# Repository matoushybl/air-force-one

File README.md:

# Air Force One - a simple air quality measurement system
Air Force One is a simple air quality measurement systems primarily designed to measure CO2 concentration in multiple rooms of a small apartment. 
It consists of nodes responsible for measuring the data and broadcasting them using BLE advertisements and a bridge which periodically receives the data and publishes them over MQTT for further processing - in this case displaying them in dashboards of Home Assistant.
There are two types of nodes which differ in used hardware and therefore communication protocol. The project was originally developed with the Bluetooth ones in mind, while the ESP32/WiFi one was added only as an experiment.

An overview of the system can be seen in the following image.

## Project structure
* `node-fw` - firmware for the Bluetooth node
* `node-c3` - firmware for the ESP32/WiFi node
* `bridge-fw` - firmware for the Bluetooth bridge
* `shared` - shared library for node and bridge firmware
* `pcb` - design files for the electronics
* `case` - design files for the case

## Hardware
The hardware for this project is based on Nordic's nRF52840 bluetooth enabled MCU. CO2 concentration, temperature and humidity are measured by a Sensirion SCD41 sensor.
The hardware was developed to allow for more features in the future so apart from the SCD41, there are more on-board parts:
* QSPI flash for measurements logging
* 4 buttons
* a connector and a hardware switch for connecting external battery (the circuitry however was not optimized for low-power even though it is well supported with embassy on nRF52)
* SHT4x sensor for more precise temperature and humidity measurements (the sensors were either badly wired or damaged on prototype boards, so no support for them was added)
* broken out pins allowing for some extensibility

The nodes and the bridge do not differ hardware wise, but the prototype bridge didn't have assembled anything other than the nRF52 module, LDO and USB circuitry to save parts, so no measurement support is available in the bridge firmware. The difference between them can be seen in the following image.

For firmware flashing a SWD probe is required. The programming connector on-board is the 10-pin Cortex-M debug connector with 1.27 mm pitch. An example of a usable probe with the same connector is the [hs-probe](https://github.com/probe-rs/hs-probe). 

There is also a case available fitting the PCB shape.

## Firmware
The firmware for both the node and the bridge is written in Rust and utilizes [embassy](https://embassy.dev) async framework as well as [nrf-softdevice](https://github.com/embassy-rs/nrf-softdevice) for bluetooth support.
As such it is assumed that you have standard embedded Rust development tools installed - such as [probe-rs](https://probe.rs/).

To use the firmware, Nordic's softdevice must first be flashed to the MCU.

1. First download the Softdevice from [here](https://www.nordicsemi.com/Software-and-tools/Software/S140/Download)
2. Mass erase the MCU `probe-rs erase --chip nrf52840_xxAA`
3. Flash the softdevice `probe-rs download --verify --format hex --chip nRF52840_xxAA s140_nrf52_7.X.X_softdevice.hex`

> Mass erasing the MCU has an unfortunate side effect of disabling reset pin. The firmwares in this repository reenable this functionality on startup.

Both of the firmware have their panic behavior configured to automatic reset, for development purposes however, it is better to switch to `panic-probe` panic handler using the 'dev' feature that can be passed to cargo.

### Node Firmware
Firmware for the node periodically reads data from the SCD41 sensor and updates Manufacturer Specific Data that are part of BLE advertisement.
For accessing the SCD41 sensor, the firmware uses the [sensirion-async](https://github.com/matoushybl/sensirion-async) library.

Flashing the firmware can be done in the `node-fw` directory by running `cargo run --release`.

### Bridge Firmware
Firmware for the bridge scans for available nodes and reads the Manufacturer Specific data part of the node's advertisement. A CDC-NCM bridge is utilized to establish a connection to a MQTT broker. Data read from the scans are then published via the broker. Static IP addresses are utilized in this configuration.

Flashing the firmware can be done in the `bridge-fw` directory by running `cargo run --release`.

## Experimental ESP32/WiFi node
As an experiment a node based on ESP32-C3 was developed. The firmware for this node is written using a similar technological stack as the nRf52 firmware - Rust and embassy. The firmware is located in the `node-c3` directory. A defining difference is that this node directly accesses the MQTT broker, making it much more simpler and hopefully more reliable.

This node also utilizes off-the-shelf hardware, so no custom PCB is requried. In this case [this ESP32-C3 board](https://www.laskakit.cz/laskkit-esp-12-board/?variantId=10482) [this SCD41 breakout board](https://www.laskakit.cz/laskakit-scd41-senzor-co2--teploty-a-vlhkosti-vzduchu/) were used, but any development kits should work the same (apart from assigning pins for the I2C).

When building the firmware SSID, password and MQTT broker address must be set as environent variables. Refer to the respective `main.rs` for environment variable names.

> As of time of publishing, the firmware uses unreleased esp-rs crates - `esp-backtrace` and `esp-println` alongside with `espflash` tool. These were used to add support for defmt.

## Accessing the measured data

### Configuring the network interface
The network interface can either be configured one-time using the `ip` command or using netplan on Ubuntu using a similar config to the one below. Using netplan has an advantage of the configuration being persistent over reboots and bridge reconnects.

The following config sets a static IP on the USB CDC-NCM interface.

```
network:
  version: 2
  renderer: networkd
  ethernets:
      enx888888888888:
          optional: true
          dhcp4: no
          addresses: [10.42.0.1/24]
```

### MQTT
The bridge firmware expects an MQTT broker running on the computer it is connected to. A simple way to spin up the broker is to use docker.
```
docker run -it -p 1883:1883 -v $(pwd)/mosquitto.conf:/mosquitto/config/mosquitto.conf eclipse-mosquitto
```

The bridge expects the broker to run without authentication, which can be achieved by the following `mosquitto.conf`:
```
listener 1883
allow_anonymous true
```

### Home Assistant
Once the measured data are published to the broker, MQTT integration in Home Assistant can be used to access the measured data. A sample Home Assistant configuration can be found below.

```yaml
mqtt:
  sensor:
    - name: "Bedroom - co2"
      state_topic: "afo-1"
      unit_of_measurement: "PPM"
      value_template: "{{ value_json.co2 }}"
      device_class: "carbon_dioxide"
    - name: "Bedroom - humidity"
      state_topic: "afo-1"
      unit_of_measurement: "%"
      value_template: "{{ value_json.humidity }}"
      device_class: "humidity"
    - name: "Bedroom - temperature"
      state_topic: "afo-1"
      unit_of_measurement: "°C"
      suggested_display_precision: 1
      value_template: "{{ value_json.temperature }}"
      device_class: "temperature"
    - name: "Living room - co2"
      state_topic: "afo-0"
      unit_of_measurement: "PPM"
      value_template: "{{ value_json.co2 }}"
      device_class: "carbon_dioxide"
    - name: "Living room - humidity"
      state_topic: "afo-0"
      unit_of_measurement: "%"
      value_template: "{{ value_json.humidity }}"
      device_class: "humidity"
    - name: "Living room - temperature"
      state_topic: "afo-0"
      unit_of_measurement: "°C"
      suggested_display_precision: 1
      value_template: "{{ value_json.temperature }}"
      device_class: "temperature"
```

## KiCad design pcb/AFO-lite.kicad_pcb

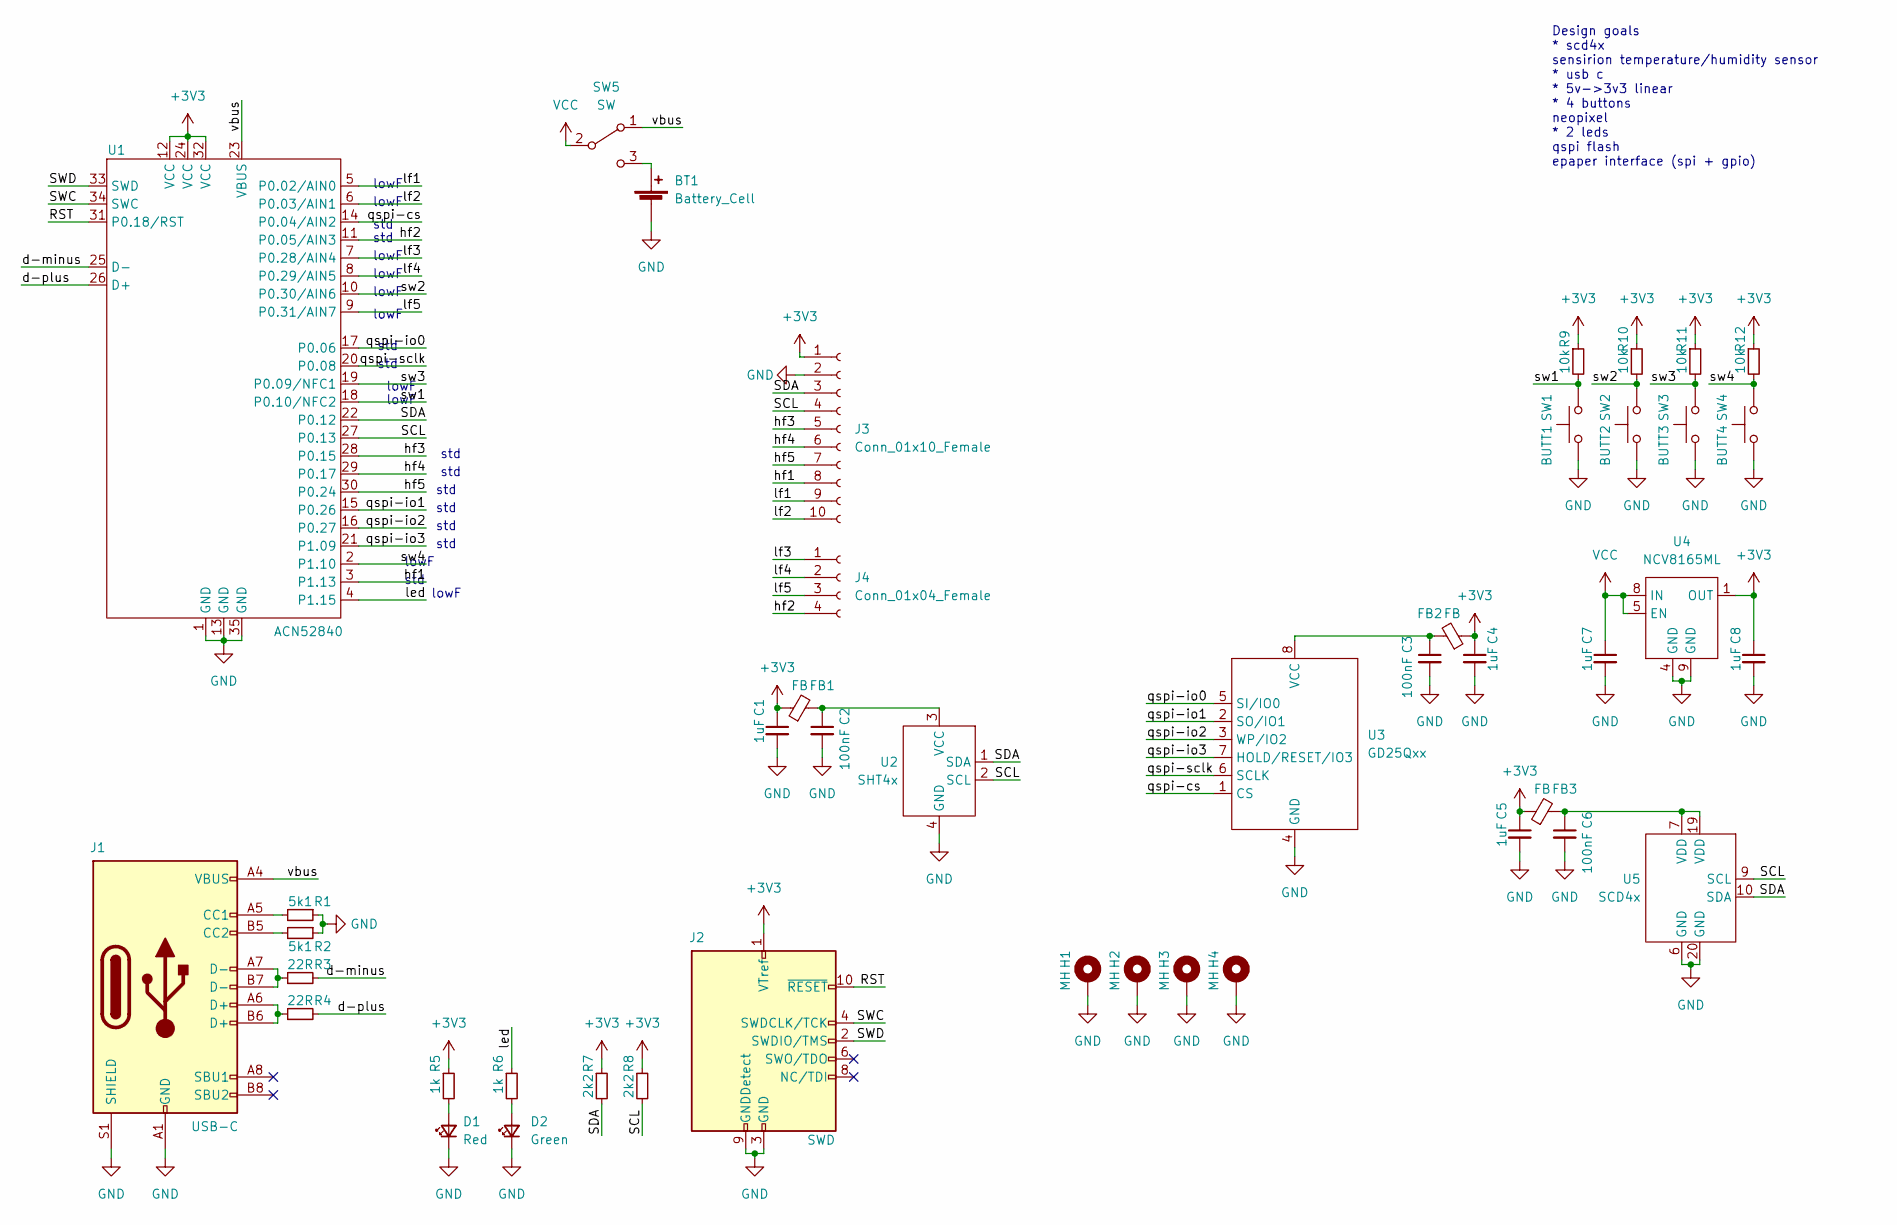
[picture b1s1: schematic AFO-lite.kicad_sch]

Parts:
BT1: Battery_Cell; PinHeader_1x02_P2.54mm_Horizontal
C1, C4, C5, C7, C8: 1uF; C_0805_2012Metric_Pad1.18x1.45mm_HandSolder
C2, C3, C6: 100nF; C_0603_1608Metric_Pad1.08x0.95mm_HandSolder
D1: Red; LED_0805_2012Metric_Pad1.15x1.40mm_HandSolder
D2: Green; LED_0805_2012Metric_Pad1.15x1.40mm_HandSolder
FB1, FB2, FB3: FB; L_0805_2012Metric_Pad1.15x1.40mm_HandSolder
H1, H2, H3, H4: MH; MountingHole_2.5mm_Pad_Via
J1: USB-C; USB_C_Receptacle_XKB_U262-16XN-4BVC11
J2: SWD; PinHeader_2x05_P1.27mm_Vertical_SMD
J3: Conn_01x10_Female; PinHeader_1x10_P2.54mm_Vertical
J4: Conn_01x04_Female; PinHeader_1x04_P2.54mm_Vertical
R1, R2: 5k1; R_0603_1608Metric_Pad0.98x0.95mm_HandSolder
R3, R4: 22R; R_0603_1608Metric_Pad0.98x0.95mm_HandSolder
R5, R6: 1k; R_0603_1608Metric_Pad0.98x0.95mm_HandSolder
R7, R8: 2k2; R_0603_1608Metric_Pad0.98x0.95mm_HandSolder
R9, R10, R11, R12: 10k; R_0603_1608Metric_Pad0.98x0.95mm_HandSolder
SW1: BUTT1; SW_SPST_B3U-3000P
SW2: BUTT2; SW_SPST_B3U-3000P
SW3: BUTT3; SW_SPST_B3U-3000P
SW4: BUTT4; SW_SPST_B3U-3000P
SW5: SW; SW_SPDT_PCM12
U1: ACN52840; ANC52840
U2: SHT4x
U3: GD25Qxx; SOP-8_5.28x5.23mm_P1.27mm
U4: NCV8165ML; DFN-8-1EP_3x3mm_P0.65mm_EP1.55x2.4mm
U5: SCD4x

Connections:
+3V3: C1.1, C4.1, C5.1, C8.1, FB1.1, FB2.1, FB3.1, J2.1 (VTref), J3.1, R5.1, R7.1, R8.1, R9.1, R10.1, R11.1, R12.1, U1.12 (VCC), U1.24 (VCC), U1.32 (VCC), U4.1 (OUT)
/RST: J2.10 (~RESET), U1.31 (P0.18/RST)
/SCL: J3.4, R8.2, U1.27 (P0.13), U2.2 (SCL), U5.9 (SCL)
/SDA: J3.3, R7.2, U1.22 (P0.12), U2.1 (SDA), U5.10 (SDA)
/SWC: J2.4 (SWDCLK/TCK), U1.34 (SWC)
/SWD: J2.2 (SWDIO/TMS), U1.33 (SWD)
/d-minus: R3.2, U1.25 (D-)
/d-plus: R4.2, U1.26 (D+)
/hf1: J3.8, U1.3 (P1.13)
/hf2: J4.4, U1.11 (P0.05/AIN3)
/hf3: J3.5, U1.28 (P0.15)
/hf4: J3.6, U1.29 (P0.17)
/hf5: J3.7, U1.30 (P0.24)
/led: R6.1, U1.4 (P1.15)
/lf1: J3.9, U1.5 (P0.02/AIN0)
/lf2: J3.10, U1.6 (P0.03/AIN1)
/lf3: J4.1, U1.7 (P0.28/AIN4)
/lf4: J4.2, U1.8 (P0.29/AIN5)
/lf5: J4.3, U1.9 (P0.31/AIN7)
/qspi-cs: U1.14 (P0.04/AIN2), U3.1 (CS)
/qspi-io0: U1.17 (P0.06), U3.5 (SI/IO0)
/qspi-io1: U1.15 (P0.26), U3.2 (SO/IO1)
/qspi-io2: U1.16 (P0.27), U3.3 (WP/IO2)
/qspi-io3: U1.21 (P1.09), U3.7 (HOLD/RESET/IO3)
/qspi-sclk: U1.20 (P0.08), U3.6 (SCLK)
/sw1: R9.2, SW1.2, U1.18 (P0.10/NFC2)
/sw2: R10.2, SW2.2, U1.10 (P0.30/AIN6)
/sw3: R11.2, SW3.2, U1.19 (P0.09/NFC1)
/sw4: R12.2, SW4.2, U1.2 (P1.10)
/vbus: J1.A4 (VBUS), J1.A9 (VBUS), J1.B4 (VBUS), J1.B9 (VBUS), SW5.1 (A), U1.23 (VBUS)
GND: BT1.2 (-), C1.2, C2.2, C3.2, C4.2, C5.2, C6.2, C7.2, C8.2, D1.1 (K), D2.1 (K), H1.1, H2.1, H3.1, H4.1, J1.A1 (GND), J1.A12 (GND), J1.B1 (GND), J1.B12 (GND), J1.S1 (SHIELD), J2.3 (GND), J2.5 (GND), J2.9 (GNDDetect), J3.2, R1.1, R2.1, SW1.1, SW2.1, SW3.1, SW4.1, U1.1 (GND), U1.13 (GND), U1.35 (GND), U2.4 (GND), U3.4 (GND), U4.4 (GND), U4.9 (GND), U5.6 (GND), U5.20 (GND)
unnamed: BT1.1 (+), SW5.3 (C)
unnamed: C2.1, FB1.2, U2.3 (VCC)
unnamed: C3.1, FB2.2, U3.8 (VCC)
unnamed: C6.1, FB3.2, U5.7 (VDD), U5.19 (VDD)
unnamed: D1.2 (A), R5.2
unnamed: D2.2 (A), R6.2
unnamed: J1.A5 (CC1), R1.2
unnamed: J1.A6 (D+), J1.B6 (D+), R4.1
unnamed: J1.A7 (D-), J1.B7 (D-), R3.1
unnamed: J1.B5 (CC2), R2.2
VCC: C7.1, SW5.2 (B), U4.5 (EN), U4.8 (IN)

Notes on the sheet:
std
lowF
Design goals * scd4x sensirion temperature/humidity sensor * usb c * 5v->3v3 linear * 4 buttons neopixel * 2 leds qspi flash epaper interface (spi + gpio)

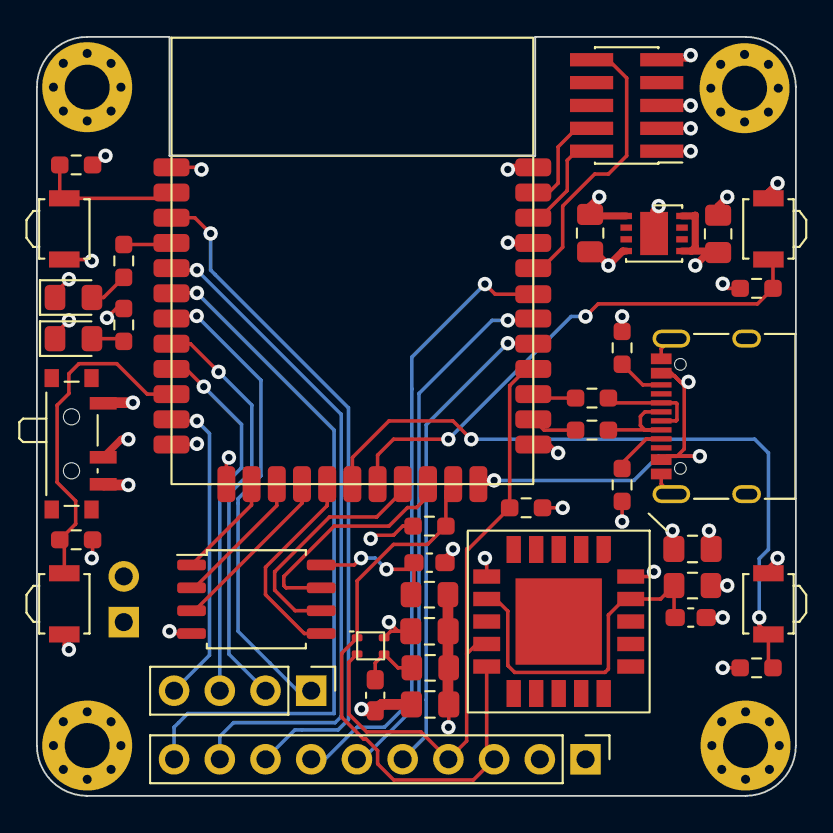
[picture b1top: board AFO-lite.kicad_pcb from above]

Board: 4 copper layers, 42.2 x 42.2 mm, 44 parts (1 on the bottom side), 42 nets.

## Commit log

2021-10-03 Initial commit.
2021-12-12 Move to embassy.
2021-12-13 Add usb logging.
2021-12-21 Improve directory structure. Add cobs.
2021-12-23 Ux updates. Fix sps data parsing.
2021-12-23 Refactor into task modules.
2021-12-24 Add VOC measurements.
2021-12-25 Show voc on display.
2021-12-27 Add softdevice. Fix problems reported by clippy.
2022-01-01 Add ble receiver and send meaingful data over BLE.
2022-01-14 refactor
2022-01-16 improve telegraf bridge
2022-07-06 ¯\_(ツ)_/¯
2022-07-08 Extract sensirion drivers to a separate library.
2022-11-18 Add support for SCD4x, bump embassy version
2022-11-18 WIP new firmware
2022-11-18 Update BLE receiver to push data over telegraf
2022-11-18 WIP HID receiver
2023-01-12 new hw support
2024-01-31 Finish v0.1
2024-02-02 Add case files
2024-02-02 Add license
2024-02-02 Fix typo in overview image
2024-02-02 Remove obsolete config folder
2024-02-11 Add esp32-c3 based node and some docs
